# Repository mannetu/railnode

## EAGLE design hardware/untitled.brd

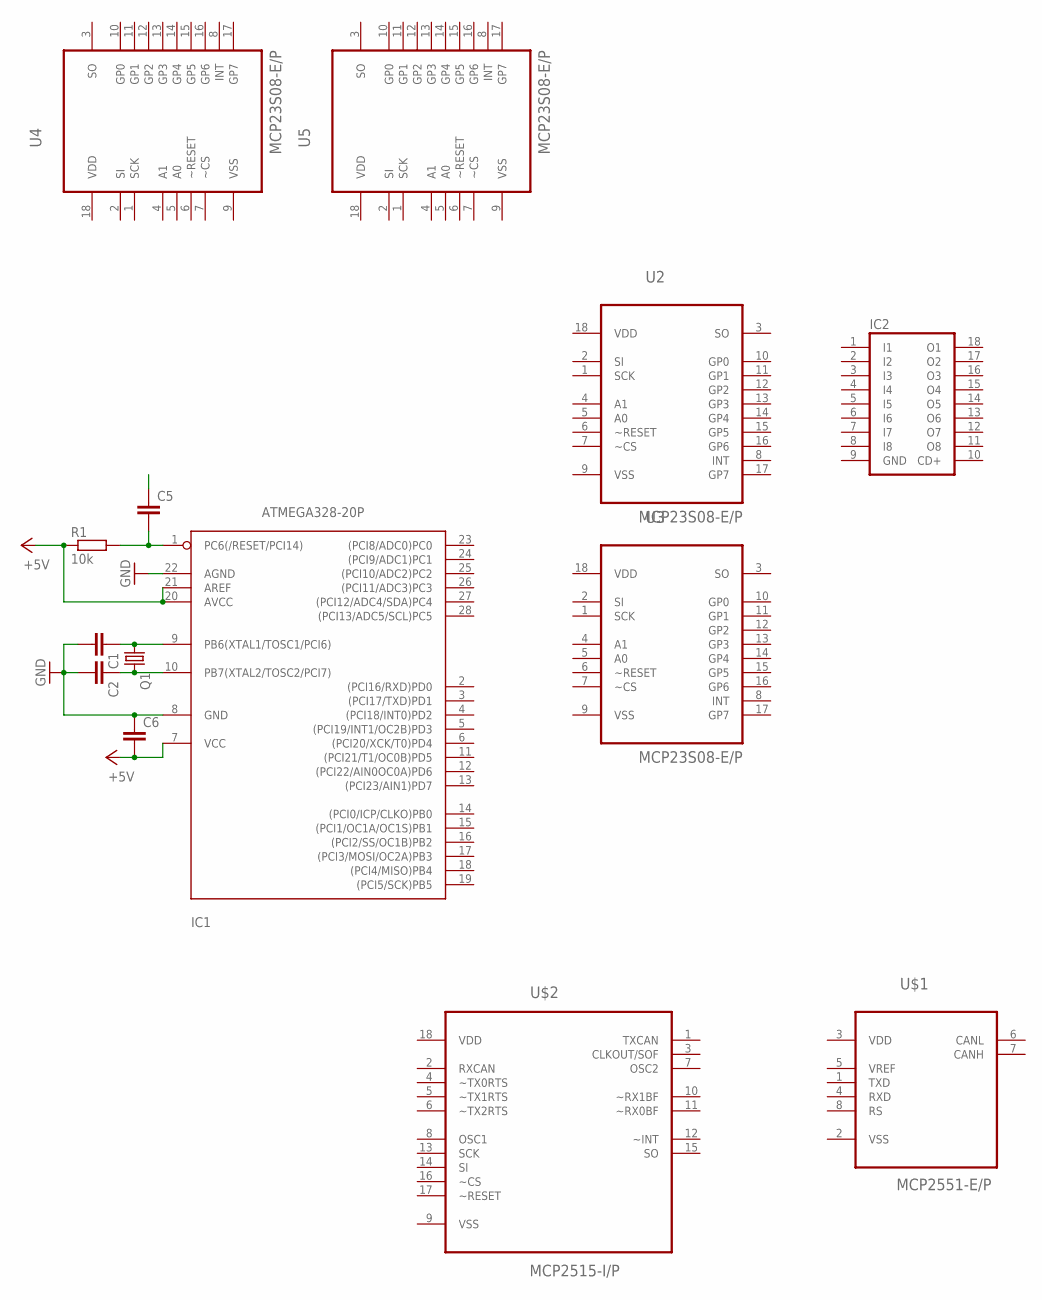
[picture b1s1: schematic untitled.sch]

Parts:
C1, C2, C5, C6: C5/3; C5B3
IC1: ATMEGA328-20P; DIL28-3
IC2: ULN2803A; DIL18
Q1: CRYSTALHC18U-V; HC18U-V
R1: 10k; 0207/12
U2, U3, U4, U5: MCP23S08-E/P; DIP254P762X432-18
U$1: MCP2551-E/P; DIP254P762X432-8
U$2: MCP2515-I/P; DIP254P762X432-18

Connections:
+5V: C6.2, IC1.7 (VCC), IC1.20 (AVCC), IC1.21 (AREF), R1.1
GND: C1.2, C2.2, C6.1, IC1.8 (GND), IC1.22 (AGND), IC2.9 (GND)
unnamed: C1.1, IC1.9 (PB6(XTAL1/TOSC1/PCI6)), Q1.1
unnamed: C2.1, IC1.10 (PB7(XTAL2/TOSC2/PCI7)), Q1.2
unnamed: C5.2, IC1.1 (PC6(/RESET/PCI14)), R1.2
VDD: U2.18 (VDD), U3.18 (VDD), U4.18 (VDD), U5.18 (VDD), U$1.3 (VDD), U$2.18 (VDD)
VSS: U2.9 (VSS), U3.9 (VSS), U4.9 (VSS), U5.9 (VSS), U$2.9 (VSS)

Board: 2 copper layers, 14 parts (0 on the bottom side), 7 nets, no tracks yet.

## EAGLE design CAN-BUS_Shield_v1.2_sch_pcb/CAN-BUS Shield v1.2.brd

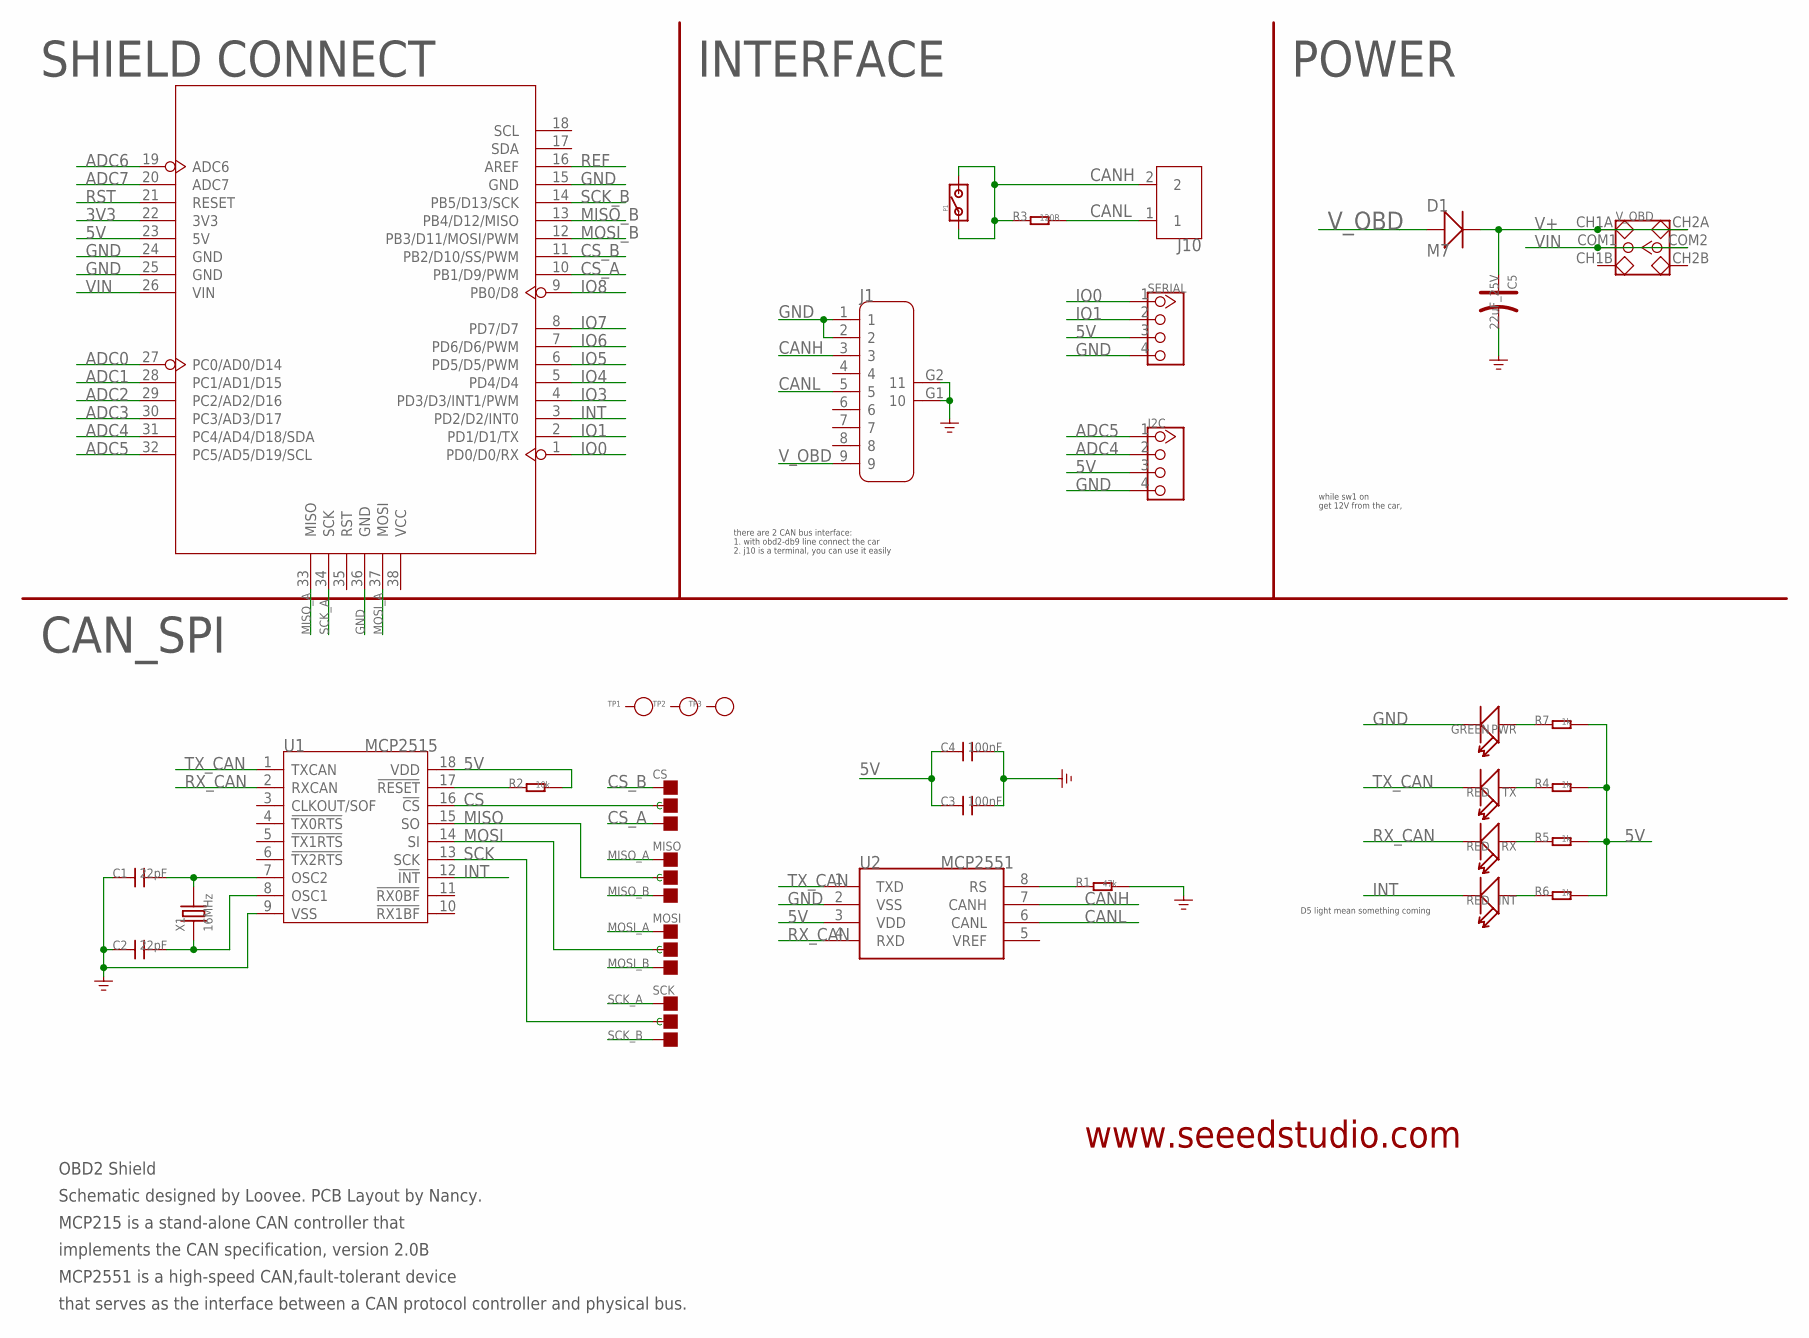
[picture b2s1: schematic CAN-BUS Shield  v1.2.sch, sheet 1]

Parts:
C1, C2: 22pF; 0603
C3, C4: 100nF; 0603
C5: 22uF_25V; ELECTRO-SMD-B-4.8MM
CS: PAD-JUMPER-3P-40*40; 3P-SMD-4.1X1.5
D1: M7; D2010
I2C: TWIG-4P-2.0-2.0; 4P-2.0
INT: RED; LED-0603
J1: DB9'MEAL'; DB9-MEAL
J10: SCREW-TERMINAL-2P5.0; 2P-5.0
MISO: PAD-JUMPER-3P-40*40; 3P-SMD-4.1X1.5
MOSI: PAD-JUMPER-3P-40*40; 3P-SMD-4.1X1.5
P1: PAD-JUMPER-2P; 2P-SMD-1.78X1.27
PWR: GREEN; LED-0603
R1: 47k; 0603
R2: 10k; 0603
R3: 120R; 0603
R4, R5, R6, R7: 1k; 0603
RX: RED; LED-0603
SCK: PAD-JUMPER-3P-40*40; 3P-SMD-4.1X1.5
SERIAL: TWIG-4P-2.0-2.0; 4P-2.0
TP1, TP2, TP3: PAD-TEST-POINT'4545'; TP_4545
TX: RED; LED-0603
U1: MCP2515; SOIC18
U2: MCP2551; SOIC8-6.0
U4: ARDUINO-38P'WITH/-SILK'; ARDUINO-38P-WITH/-SILK-500519002
V_OBD: SWITCH-2CH-6P; 6P-2CH-2.54-7.6X3.0
X1: 16MHz; HC49/S

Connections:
3V3: U4.22 (3V3)
5V: C3.1, C4.1, I2C.3, R2.2, R4.2, R5.2, R6.2, R7.2, SERIAL.3, U1.18 (VDD), U2.3 (VDD), U4.23 (5V)
ADC0: U4.27 (PC0/AD0/D14)
ADC1: U4.28 (PC1/AD1/D15)
ADC2: U4.29 (PC2/AD2/D16)
ADC3: U4.30 (PC3/AD3/D17)
ADC4: I2C.2, U4.31 (PC4/AD4/D18/SDA)
ADC5: I2C.1, U4.32 (PC5/AD5/D19/SCL)
ADC6: U4.19 (ADC6)
ADC7: U4.20 (ADC7)
CANH: J1.3, J10.2, P1.1, P1.2, R3.1, U2.7 (CANH)
CANL: J1.5, J10.1, R3.2, U2.6 (CANL)
CS: CS.MM (C), U1.16 (!CS)
CS_A: CS.11 (R), U4.10 (PB1/D9/PWM)
CS_B: CS.00 (L), U4.11 (PB2/D10/SS/PWM)
GND: C1.1, C2.1, C3.2, C4.2, C5.-, I2C.4, J1.1, J1.2, J1.G1 (10), J1.G2 (11), PWR.-, R1.2, SERIAL.4, U1.9 (VSS), U2.2 (VSS), U4.15 (GND), U4.24 (GND), U4.25 (GND), U4.36 (GND)
INT: INT.-, U1.12 (!INT), U4.3 (PD2/D2/INT0)
IO0: SERIAL.1, U4.1 (PD0/D0/RX)
IO1: SERIAL.2, U4.2 (PD1/D1/TX)
IO3: U4.4 (PD3/D3/INT1/PWM)
IO4: U4.5 (PD4/D4)
IO5: U4.6 (PD5/D5/PWM)
IO6: U4.7 (PD6/D6/PWM)
IO7: U4.8 (PD7/D7)
IO8: U4.9 (PB0/D8)
MISO: MISO.MM (C), U1.15 (SO)
MISO_A: MISO.00 (L), U4.33 (MISO)
MISO_B: MISO.11 (R), U4.13 (PB4/D12/MISO)
MOSI: MOSI.MM (C), U1.14 (SI)
MOSI_A: MOSI.00 (L), U4.37 (MOSI)
MOSI_B: MOSI.11 (R), U4.12 (PB3/D11/MOSI/PWM)
unnamed: PWR.+, R7.1
unnamed: R4.1, TX.+
unnamed: R5.1, RX.+
unnamed: C1.2, U1.7 (OSC2), X1.2
unnamed: C2.2, U1.8 (OSC1), X1.1
unnamed: INT.+, R6.1
unnamed: R1.1, U2.8 (RS)
REF: U4.16 (AREF)
RST: U4.21 (RESET)
RST_N: R2.1, U1.17 (!RESET)
RX_CAN: RX.-, U1.2 (RXCAN), U2.4 (RXD)
SCK: SCK.MM (C), U1.13 (SCK)
SCK_A: SCK.00 (L), U4.34 (SCK)
SCK_B: SCK.11 (R), U4.14 (PB5/D13/SCK)
TX_CAN: TX.-, U1.1 (TXCAN), U2.1 (TXD)
V+: C5.+, D1.-, V_OBD.CH1A, V_OBD.CH2A
VIN: U4.26 (VIN), V_OBD.COM1, V_OBD.COM2
V_OBD: D1.+, J1.9

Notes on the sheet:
CAN_SPI
SHIELD CONNECT
INTERFACE
POWER
get 12V from the car,
D5 light mean something coming
OBD2 Shield
Schematic designed by Loovee. PCB Layout by Nancy.
MCP215 is a stand-alone CAN controller that
MCP2551 is a high-speed CAN,fault-tolerant device
that serves as the interface between a CAN protocol controller and physical bus.
implements the CAN specification, version 2.0B
www.seeedstudio.com
while sw1 on
there are 2 CAN bus interface:
1. with obd2-db9 line connect the car
2. j10 is a terminal, you can use it easily

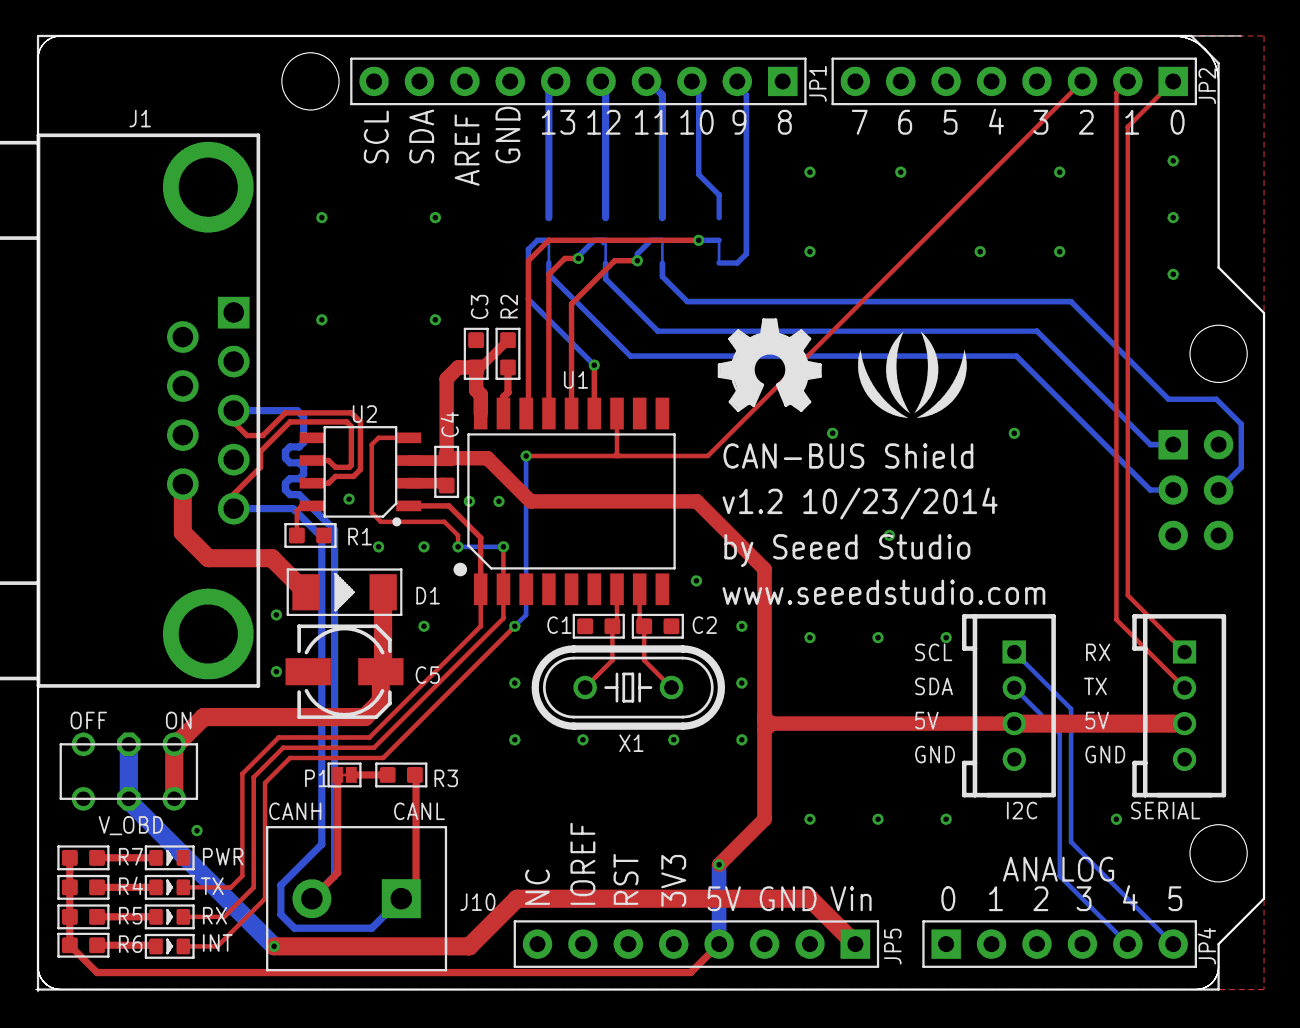
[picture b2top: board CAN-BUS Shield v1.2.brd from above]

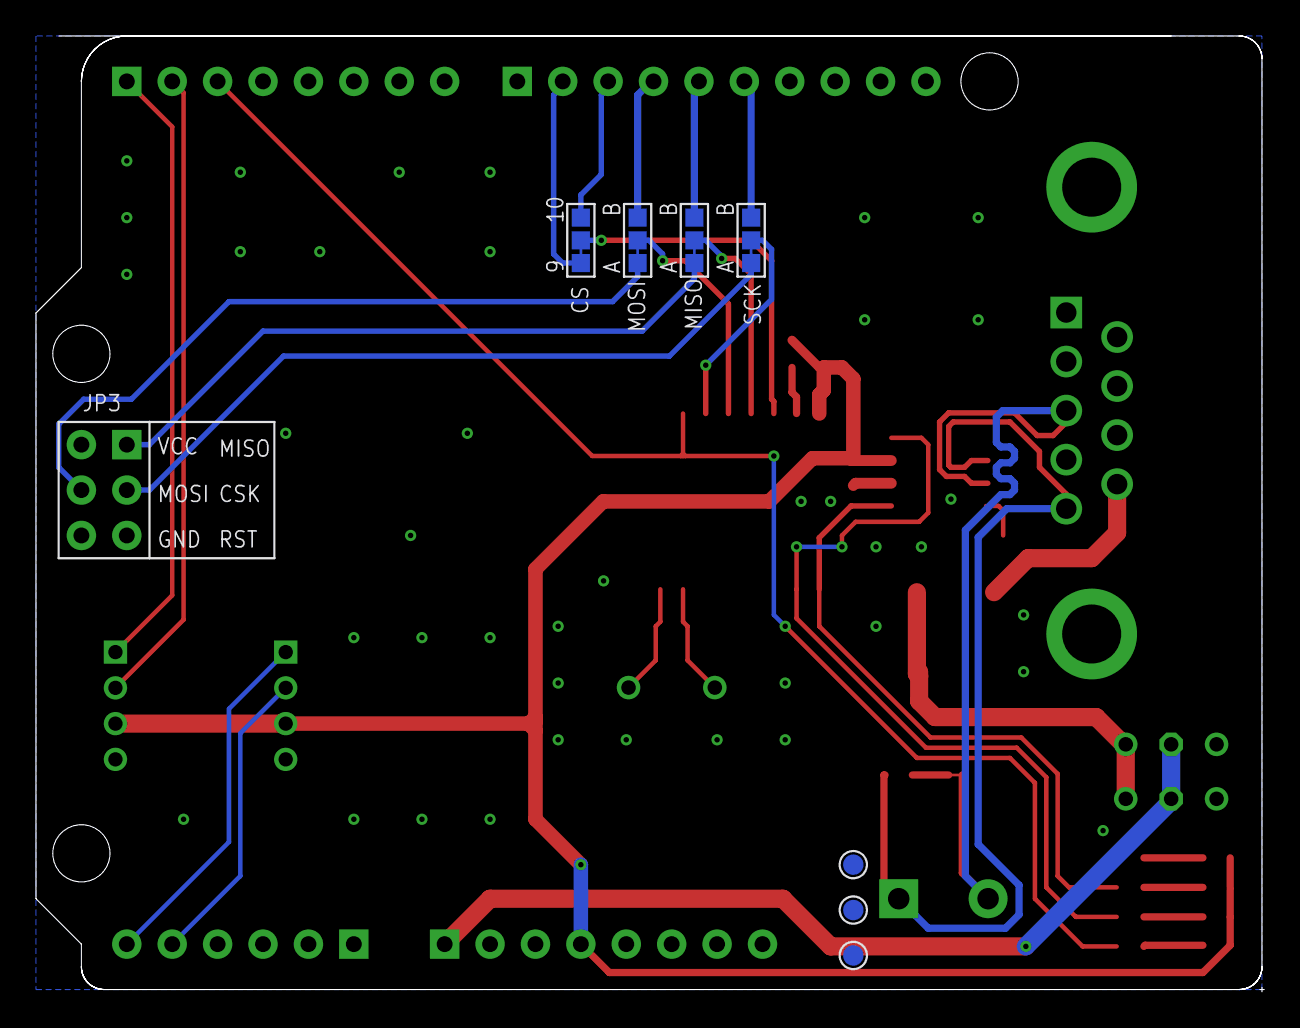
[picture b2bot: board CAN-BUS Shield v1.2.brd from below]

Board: 2 copper layers, 68.6 x 53.3 mm, 36 parts (7 on the bottom side), 34 nets.

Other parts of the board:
U$1: LOGO_SILK
U$2: OSHW_FILLX200_NOTEXT

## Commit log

2016-09-12 blubb
2016-09-19 lesen/schreiben funktioniert mit Raspi
2016-12-10 serial monitor
2016-12-21 läuft
2016-12-28 added turnout reporter
2016-12-29 funkt
2017-01-03 added 2nd turnout
